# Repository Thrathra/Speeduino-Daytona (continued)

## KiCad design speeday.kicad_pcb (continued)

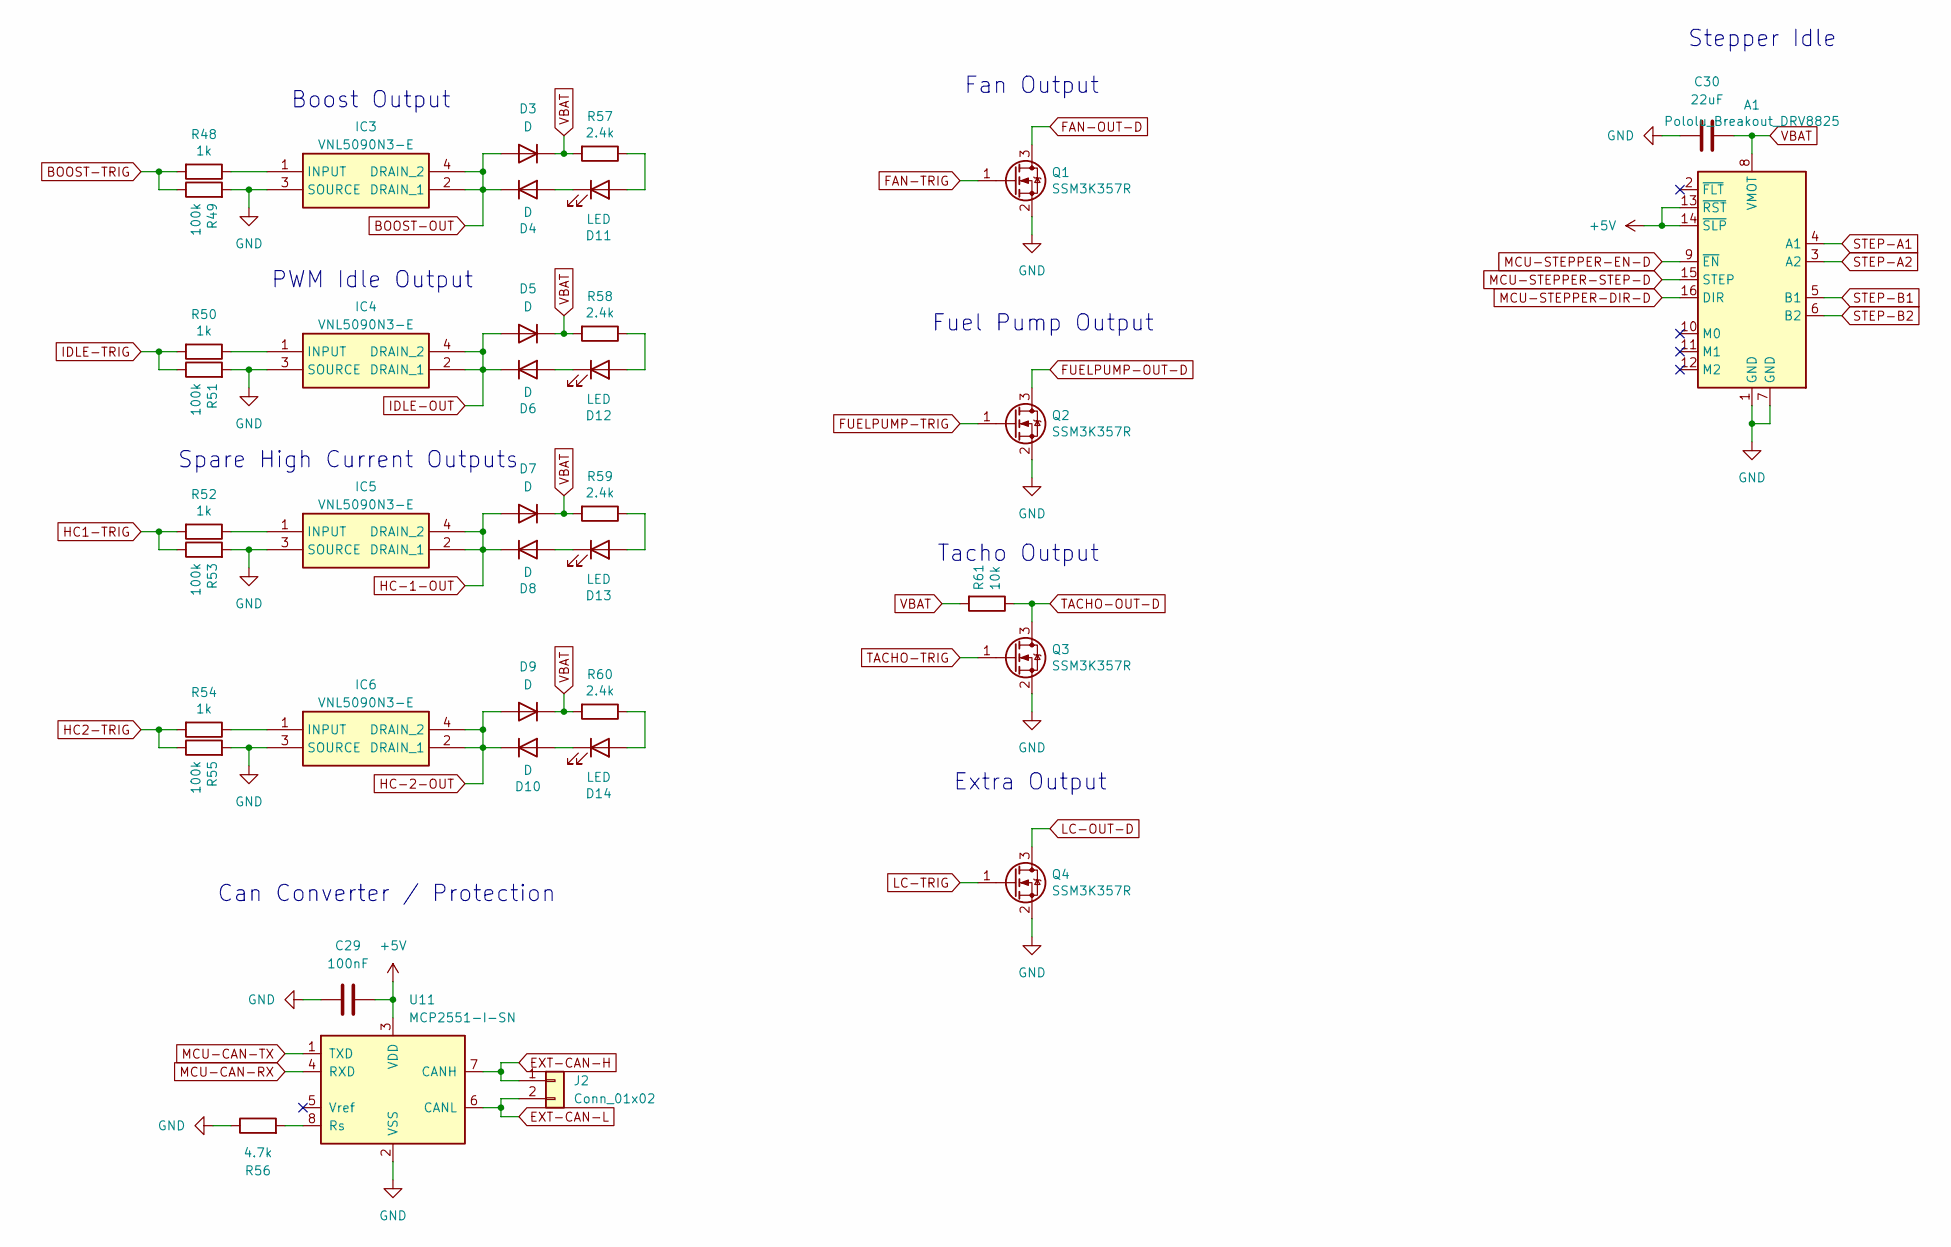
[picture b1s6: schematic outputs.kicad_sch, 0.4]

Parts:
A1: Pololu_Breakout_DRV8825; Pololu_Breakout-16_15.2x20.3mm
C29: 100nF; C_0805_2012Metric
C30: 22uF; C_0805_2012Metric
D3, D5, D7, D9: D; D_SOD-323
D4, D6, D8, D10: D; D_SOD-323; Manufacturer_Part_Number 1N4448WX-TP; Digikey Part Number 1N4448WXTPMSCT-ND
D11, D12, D13, D14: LED; LED_0805_2012Metric; Manufacturer_Part_Number LH R974-LP-1; Digikey Part Number 475-1415-1-ND
IC3, IC4, IC5, IC6: VNL5090N3-E; SOT230P700X180-4N; Manufacturer_Part_Number VNL5090N3-E
J2: Conn_01x02; PinHeader_1x02_P2.54mm_Vertical
Q1, Q2, Q3, Q4: SSM3K357R; SOT-23; Manufacturer_Part_Number SSM3K357R; Digikey Part Number SSM3K357RLFCT-ND
R48, R50, R52, R54: 1k; R_0805_2012Metric; Manufacturer_Part_Number RC0805FR-071KL; Digikey Part Number 311-1.00KCRCT-ND
R49, R51, R53, R55: 100k; R_0805_2012Metric; Manufacturer_Part_Number RC0805FR-07100KL; Digikey Part Number 311-100KCRCT-ND
R56: 4.7k; R_0805_2012Metric
R57, R58, R59, R60: 2.4k; R_0805_2012Metric; Manufacturer_Part_Number RC0805FR-072K4L; Digikey Part Number 311-2.40KCRCT-ND
R61: 10k; R_0805_2012Metric; Manufacturer_Part_Number RC0805JR-0710KL; Digikey Part Number 311-10KARCT-ND
U11: MCP2551-I-SN; SOIC-8_3.9x4.9mm_P1.27mm

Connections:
+5V: A1.13 (~RST), A1.14 (~SLP), C29.2, U11.3 (VDD); also elsewhere on the board
BOOST-OUT: D3.2 (A), D4.1 (K), IC3.2 (DRAIN_1), IC3.4 (DRAIN_2); also elsewhere on the board
BOOST-TRIG: R48.2, R49.1; also elsewhere on the board
EXT-CAN-H: J2.1, U11.7 (CANH)
EXT-CAN-L: J2.2, U11.6 (CANL)
FAN-OUT-D: Q1.3 (D); also elsewhere on the board
FAN-TRIG: Q1.1 (G); also elsewhere on the board
FUELPUMP-OUT-D: Q2.3 (D); also elsewhere on the board
FUELPUMP-TRIG: Q2.1 (G); also elsewhere on the board
GND: A1.1 (GND), A1.7 (GND), C29.1, C30.1, IC3.3 (SOURCE), IC4.3 (SOURCE), IC5.3 (SOURCE), IC6.3 (SOURCE), Q1.2 (S), Q2.2 (S), Q3.2 (S), Q4.2 (S), R49.2, R51.2, R53.2, R55.2, R56.1, U11.2 (VSS); also elsewhere on the board
HC1-TRIG: R52.2, R53.1; also elsewhere on the board
HC2-TRIG: R54.2, R55.1; also elsewhere on the board
HC-1-OUT: D7.2 (A), D8.1 (K), IC5.2 (DRAIN_1), IC5.4 (DRAIN_2); also elsewhere on the board
HC-2-OUT: D9.2 (A), D10.1 (K), IC6.2 (DRAIN_1), IC6.4 (DRAIN_2); also elsewhere on the board
IDLE-OUT: D5.2 (A), D6.1 (K), IC4.2 (DRAIN_1), IC4.4 (DRAIN_2); also elsewhere on the board
IDLE-TRIG: R50.2, R51.1; also elsewhere on the board
LC-OUT-D: Q4.3 (D); also elsewhere on the board
LC-TRIG: Q4.1 (G); also elsewhere on the board
MCU-CAN-RX: U11.4 (RXD); also elsewhere on the board
MCU-CAN-TX: U11.1 (TXD); also elsewhere on the board
MCU-STEPPER-DIR-D: A1.16 (DIR); also elsewhere on the board
MCU-STEPPER-EN-D: A1.9 (~EN); also elsewhere on the board
MCU-STEPPER-STEP-D: A1.15 (STEP); also elsewhere on the board
unnamed: D10.2 (A), D14.1 (K)
unnamed: D11.2 (A), R57.1
unnamed: D4.2 (A), D11.1 (K)
unnamed: D12.2 (A), R58.1
unnamed: D6.2 (A), D12.1 (K)
unnamed: D13.2 (A), R59.1
unnamed: D8.2 (A), D13.1 (K)
unnamed: D14.2 (A), R60.1
unnamed: IC3.1 (INPUT), R48.1
unnamed: IC4.1 (INPUT), R50.1
unnamed: IC5.1 (INPUT), R52.1
unnamed: IC6.1 (INPUT), R54.1
unnamed: R56.2, U11.8 (Rs)
STEP-A1: A1.4 (A1); also elsewhere on the board
STEP-A2: A1.3 (A2); also elsewhere on the board
STEP-B1: A1.5 (B1); also elsewhere on the board
STEP-B2: A1.6 (B2); also elsewhere on the board
TACHO-OUT-D: Q3.3 (D), R61.1; also elsewhere on the board
TACHO-TRIG: Q3.1 (G); also elsewhere on the board
VBAT: A1.8 (VMOT), C30.2, D3.1 (K), D5.1 (K), D7.1 (K), D9.1 (K), R57.2, R58.2, R59.2, R60.2, R61.2; also elsewhere on the board

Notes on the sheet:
Stepper Idle
Extra Output
PWM Idle Output
Spare High Current Outputs
Fan Output
Fuel Pump Output
Boost Output
Tacho Output
Can Converter / Protection

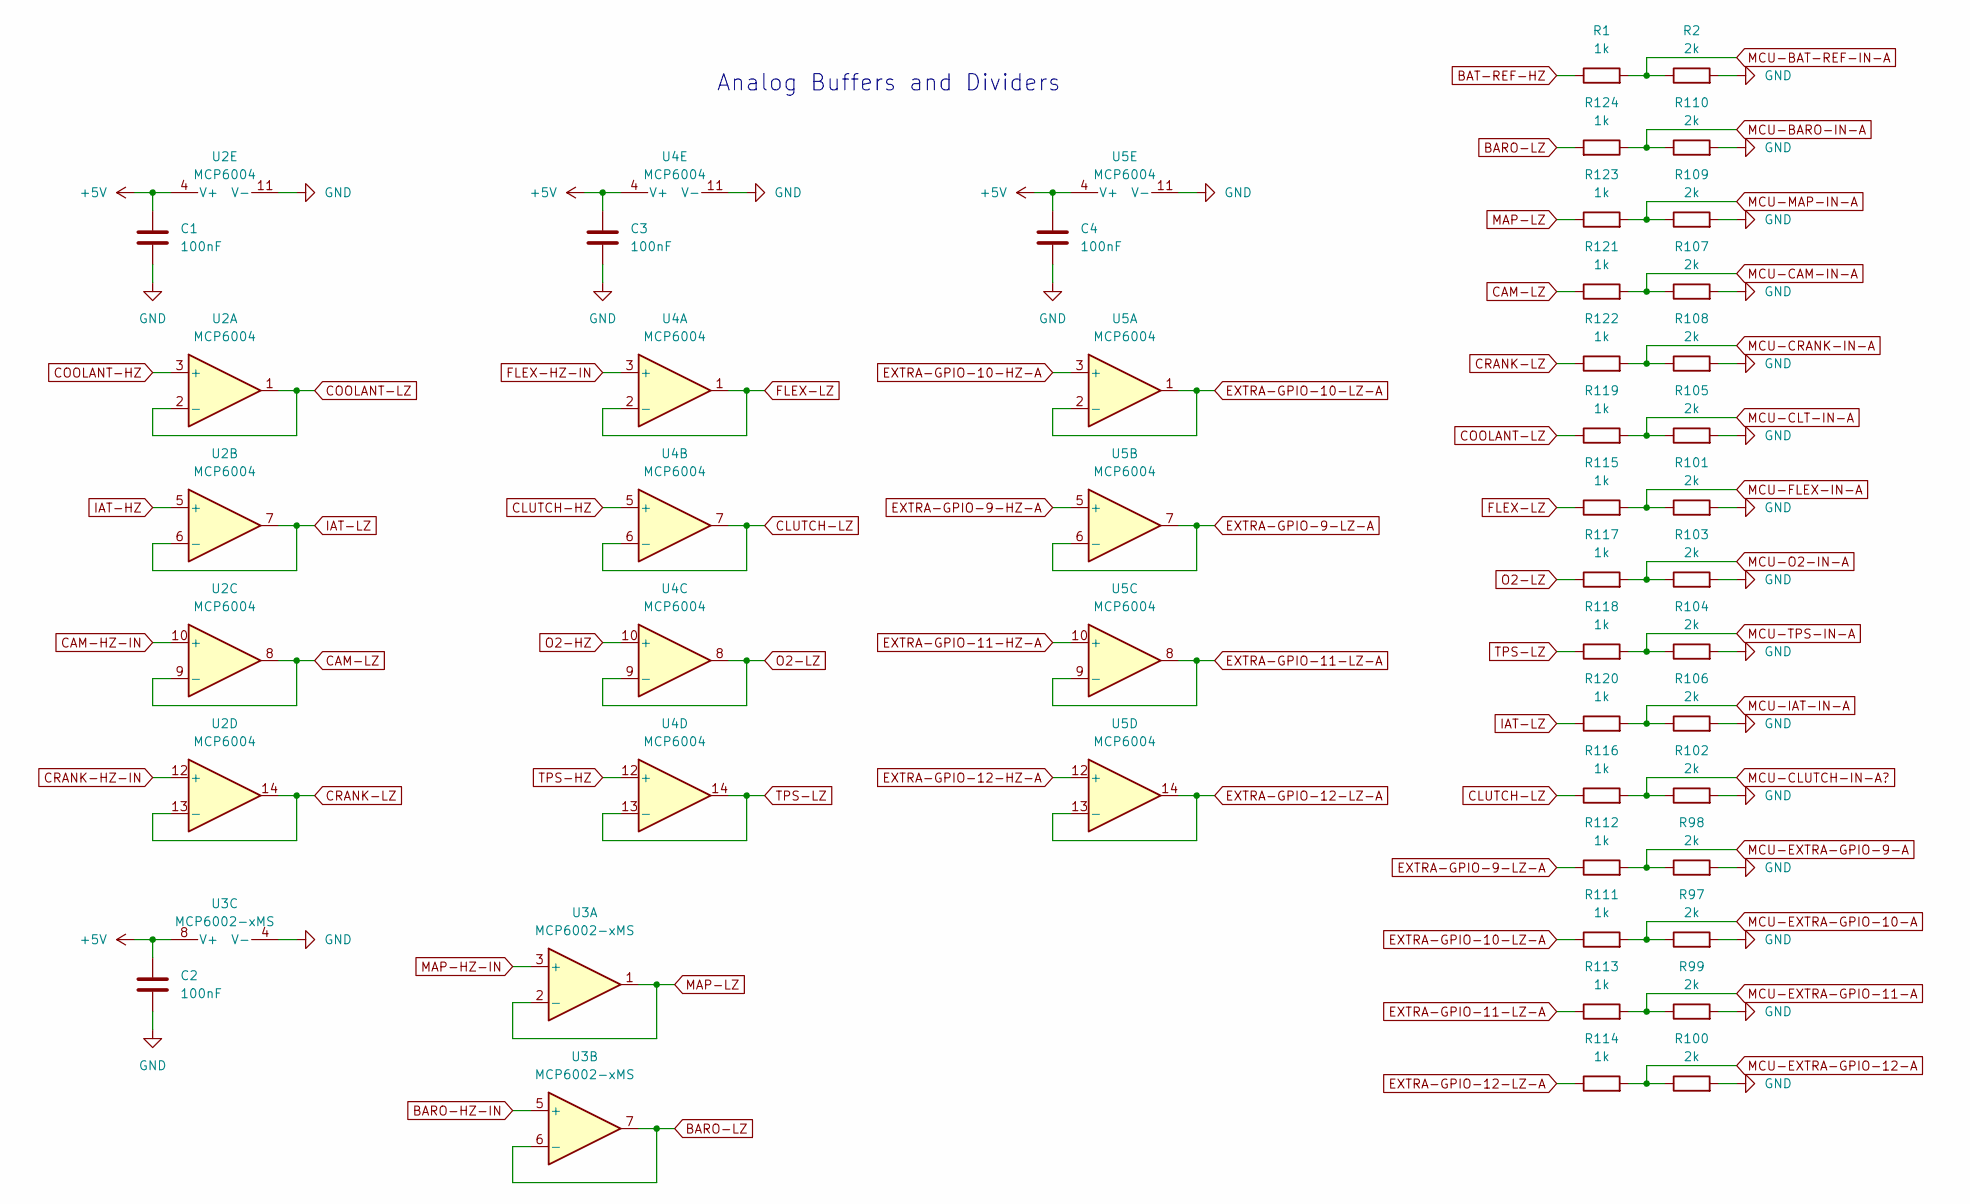
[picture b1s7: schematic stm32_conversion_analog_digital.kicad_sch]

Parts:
C1, C2, C3, C4: 100nF; C_0805_2012Metric
R1, R111, R112, R113, R114, R115, R116, R117, R118, R119, R120, R121, R122, R123, R124: 1k; R_0805_2012Metric
R2, R97, R98, R99, R100, R101, R102, R103, R104, R105, R106, R107, R108, R109, R110: 2k; R_0805_2012Metric
U2, U4, U5: MCP6004; TSSOP-14_4.4x5mm_P0.65mm
U3: MCP6002-xMS; TSSOP-8_4.4x3mm_P0.65mm

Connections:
+5V: C1.1, C2.1, C3.1, C4.1, U2.4 (V+), U3.8 (V+), U4.4 (V+), U5.4 (V+); also elsewhere on the board
BARO-HZ-IN: U3.5 (+); also elsewhere on the board
BARO-LZ: R124.2, U3.6 (-), U3.7
BAT-REF-HZ: R1.1; also elsewhere on the board
CAM-HZ-IN: U2.10 (+); also elsewhere on the board
CAM-LZ: R121.1, U2.8, U2.9 (-)
CLUTCH-HZ: U4.5 (+); also elsewhere on the board
CLUTCH-LZ: R116.1, U4.6 (-), U4.7
COOLANT-HZ: U2.3 (+); also elsewhere on the board
COOLANT-LZ: R119.1, U2.1, U2.2 (-)
CRANK-HZ-IN: U2.12 (+); also elsewhere on the board
CRANK-LZ: R122.1, U2.13 (-), U2.14
EXTRA-GPIO-9-HZ-A: U5.5 (+); also elsewhere on the board
EXTRA-GPIO-9-LZ-A: R112.1, U5.6 (-), U5.7
EXTRA-GPIO-10-HZ-A: U5.3 (+); also elsewhere on the board
EXTRA-GPIO-10-LZ-A: R111.1, U5.1, U5.2 (-)
EXTRA-GPIO-11-HZ-A: U5.10 (+); also elsewhere on the board
EXTRA-GPIO-11-LZ-A: R113.1, U5.8, U5.9 (-)
EXTRA-GPIO-12-HZ-A: U5.12 (+); also elsewhere on the board
EXTRA-GPIO-12-LZ-A: R114.1, U5.13 (-), U5.14
FLEX-HZ-IN: U4.3 (+); also elsewhere on the board
FLEX-LZ: R115.1, U4.1, U4.2 (-)
GND: C1.2, C2.2, C3.2, C4.2, R2.2, R97.2, R98.2, R99.2, R100.2, R101.2, R102.2, R103.2, R104.2, R105.2, R106.2, R107.2, R108.2, R109.2, R110.2, U2.11 (V-), U3.4 (V-), U4.11 (V-), U5.11 (V-); also elsewhere on the board
IAT-HZ: U2.5 (+); also elsewhere on the board
IAT-LZ: R120.1, U2.6 (-), U2.7
MAP-HZ-IN: U3.3 (+); also elsewhere on the board
MAP-LZ: R123.1, U3.1, U3.2 (-)
MCU-BARO-IN-A: R110.1, R124.1; also elsewhere on the board
MCU-BAT-REF-IN-A: R1.2, R2.1; also elsewhere on the board
MCU-CAM-IN-A: R107.1, R121.2; also elsewhere on the board
MCU-CLT-IN-A: R105.1, R119.2; also elsewhere on the board
MCU-CLUTCH-IN-A?: R102.1, R116.2; also elsewhere on the board
MCU-CRANK-IN-A: R108.1, R122.2; also elsewhere on the board
MCU-EXTRA-GPIO-9-A: R98.1, R112.2; also elsewhere on the board
MCU-EXTRA-GPIO-10-A: R97.1, R111.2; also elsewhere on the board
MCU-EXTRA-GPIO-11-A: R99.1, R113.2; also elsewhere on the board
MCU-EXTRA-GPIO-12-A: R100.1, R114.2; also elsewhere on the board
MCU-FLEX-IN-A: R101.1, R115.2; also elsewhere on the board
MCU-IAT-IN-A: R106.1, R120.2; also elsewhere on the board
MCU-MAP-IN-A: R109.1, R123.2; also elsewhere on the board
MCU-O2-IN-A: R103.1, R117.2; also elsewhere on the board
MCU-TPS-IN-A: R104.1, R118.2; also elsewhere on the board
O2-HZ: U4.10 (+); also elsewhere on the board
O2-LZ: R117.1, U4.8, U4.9 (-)
TPS-HZ: U4.12 (+); also elsewhere on the board
TPS-LZ: R118.1, U4.13 (-), U4.14

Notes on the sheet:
Analog Buffers and Dividers

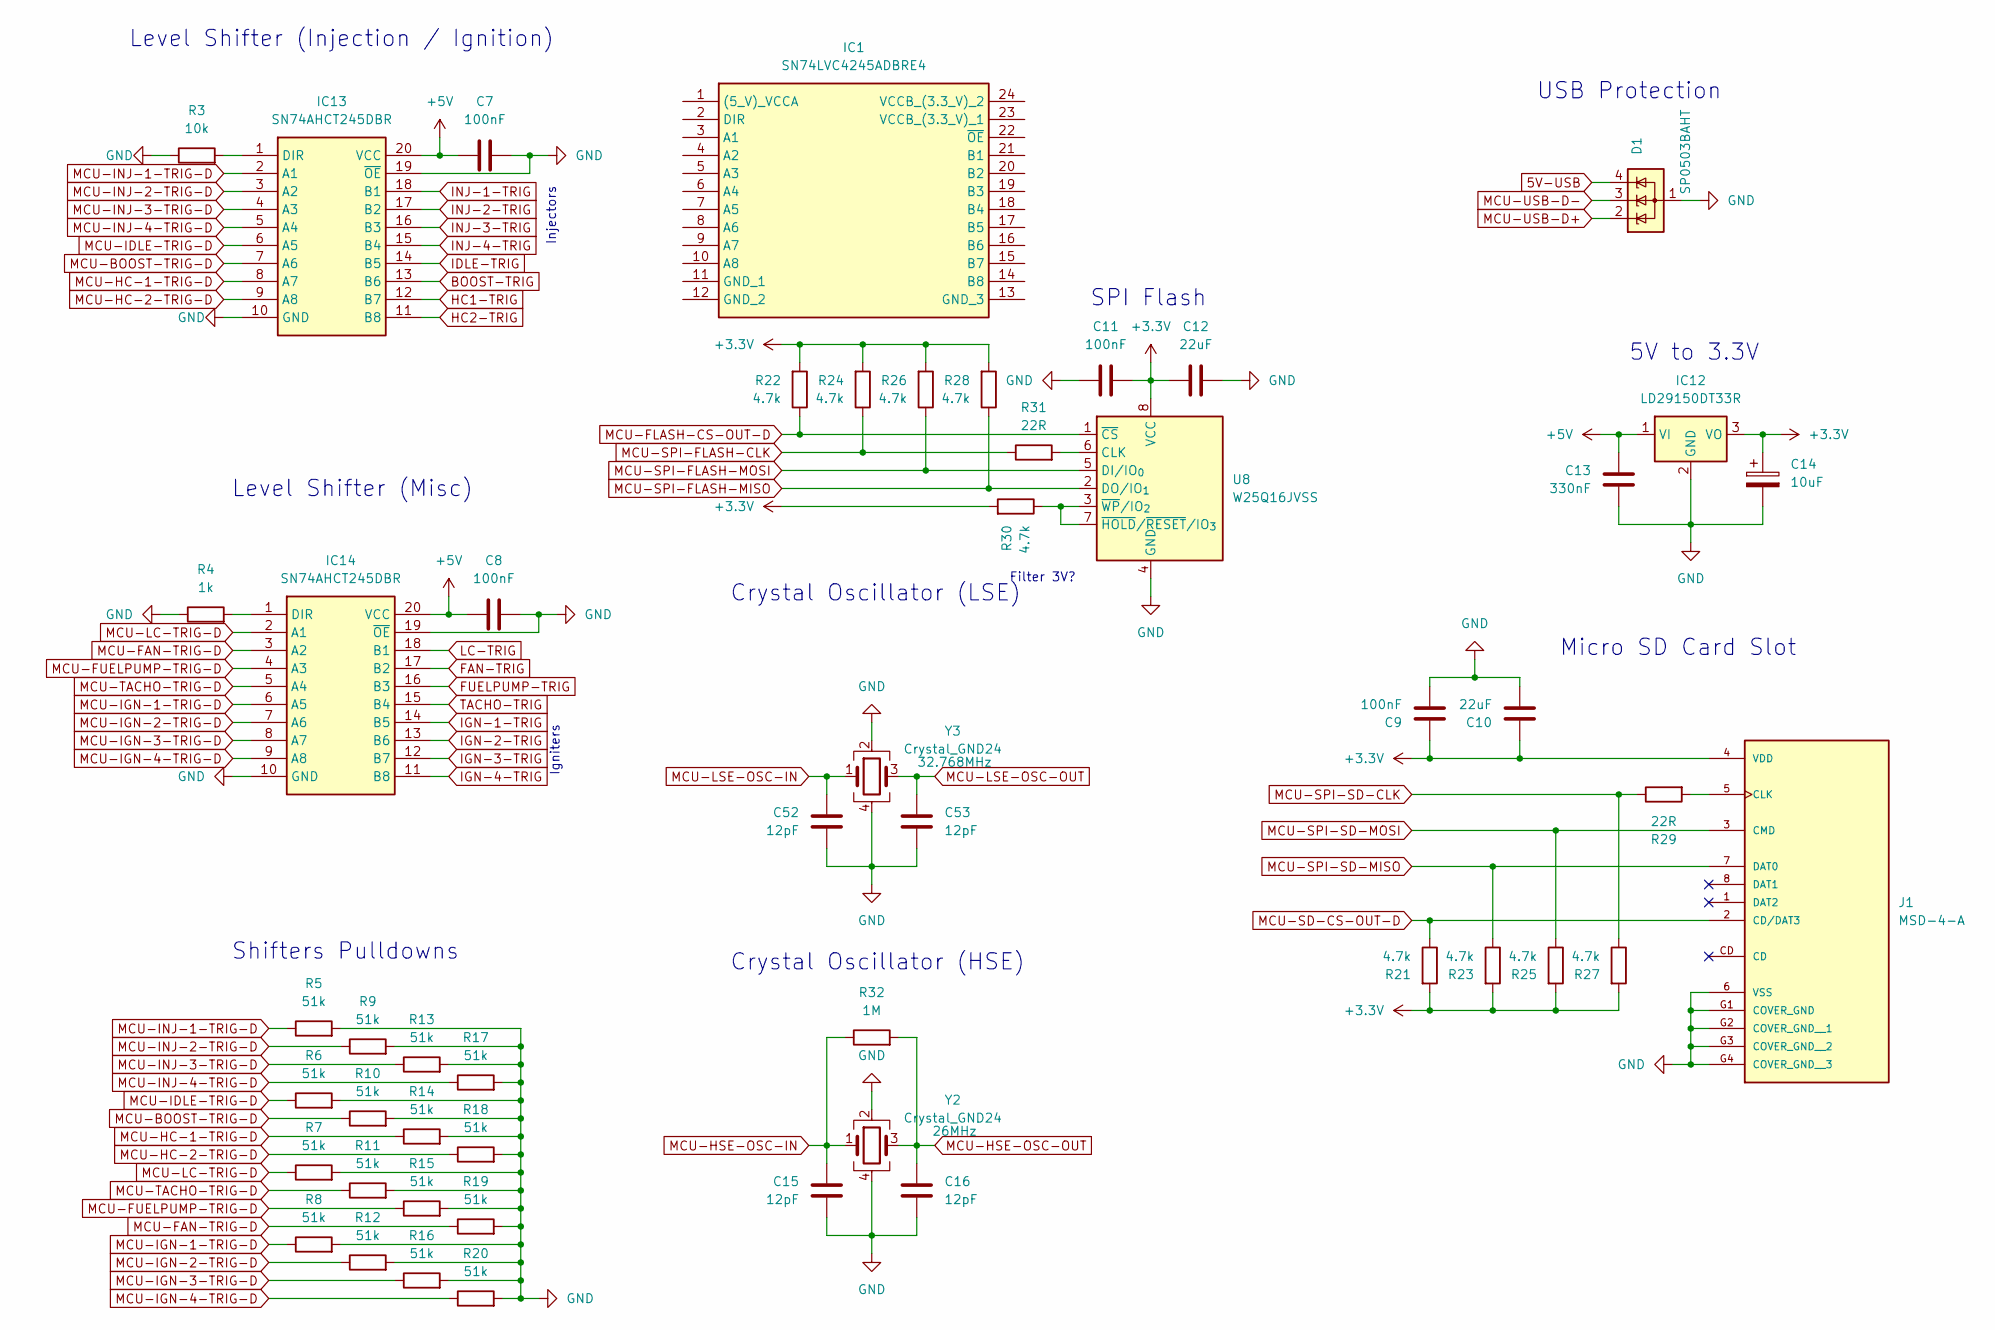
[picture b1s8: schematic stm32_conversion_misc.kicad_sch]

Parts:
C7, C8, C9, C11: 100nF; C_0805_2012Metric
C10, C12: 22uF; C_0805_2012Metric
C13: 330nF; C_0805_2012Metric
C14: 10uF; CP_EIA-3528-12_Kemet-T
C15, C16, C52, C53: 12pF; C_0805_2012Metric
D1: SP0503BAHT; SOT-143
IC1: SN74LVC4245ADBRE4; SOP65P780X200-24N; Manufacturer_Part_Number SN74LVC4245ADBRE4; Mouser Part Number 595-SN74LVC4245ADBRE
IC12: LD29150DT33R; TO-252-2; Manufacturer_Part_Number LD29150DT33R; Mouser Part Number 511-LD29150DT33R
IC13, IC14: SN74AHCT245DBR; SOP65P780X200-20N; Manufacturer_Part_Number SN74AHCT245DBR; Mouser Part Number 595-SN74AHCT245DBR
J1: MSD-4-A; CUI_MSD-4-A; PARTREV 1.0
R3: 10k; R_0805_2012Metric
R4: 1k; R_0805_2012Metric
R5, R6, R7, R8, R9, R10, R11, R12, R13, R14, R15, R16, R17, R18, R19, R20: 51k; R_0805_2012Metric
R21, R22, R23, R24, R25, R26, R27, R28, R30: 4.7k; R_0805_2012Metric
R29, R31: 22R; R_0805_2012Metric
R32: 1M; R_0805_2012Metric
U8: W25Q16JVSS; SOIC-8_5.3x5.3mm_P1.27mm
Y2, Y3: Crystal_GND24; Crystal_SMD_2016-4Pin_2.0x1.6mm

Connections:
5V-USB: D1.4 (K); also elsewhere on the board
+3.3V: C9.2, C10.2, C11.2, C12.1, C14.1, IC12.3 (VO), J1.4 (VDD), R21.2, R22.2, R23.2, R24.2, R25.2, R26.2, R27.2, R28.2, R30.2, U8.8 (VCC); also elsewhere on the board
+5V: C7.1, C8.1, C13.1, IC12.1 (VI), IC13.20 (VCC), IC14.20 (VCC); also elsewhere on the board
BOOST-TRIG: IC13.13 (B6); also elsewhere on the board
FAN-TRIG: IC14.17 (B2); also elsewhere on the board
FUELPUMP-TRIG: IC14.16 (B3); also elsewhere on the board
GND: C7.2, C8.2, C9.1, C10.1, C11.1, C12.2, C13.2, C14.2, C15.2, C16.2, C52.2, C53.2, D1.1 (A), IC12.2 (GND), IC13.10 (GND), IC13.19 (~OE), IC14.10 (GND), IC14.19 (~OE), J1.6 (VSS), J1.G1 (COVER_GND), J1.G2 (COVER_GND__1), J1.G3 (COVER_GND__2), J1.G4 (COVER_GND__3), R3.1, R4.1, R5.2, R6.2, R7.2, R8.2, R9.2, R10.2, R11.2, R12.2, R13.2, R14.2, R15.2, R16.2, R17.2, R18.2, R19.2, R20.2, U8.4 (GND), Y2.2, Y2.4, Y3.2, Y3.4; also elsewhere on the board
HC1-TRIG: IC13.12 (B7); also elsewhere on the board
HC2-TRIG: IC13.11 (B8); also elsewhere on the board
IDLE-TRIG: IC13.14 (B5); also elsewhere on the board
IGN-1-TRIG: IC14.14 (B5); also elsewhere on the board
IGN-2-TRIG: IC14.13 (B6); also elsewhere on the board
IGN-3-TRIG: IC14.12 (B7); also elsewhere on the board
IGN-4-TRIG: IC14.11 (B8); also elsewhere on the board
INJ-1-TRIG: IC13.18 (B1); also elsewhere on the board
INJ-2-TRIG: IC13.17 (B2); also elsewhere on the board
INJ-3-TRIG: IC13.16 (B3); also elsewhere on the board
INJ-4-TRIG: IC13.15 (B4); also elsewhere on the board
LC-TRIG: IC14.18 (B1); also elsewhere on the board
MCU-BOOST-TRIG-D: IC13.7 (A6), R10.1; also elsewhere on the board
MCU-FAN-TRIG-D: IC14.3 (A2), R19.1; also elsewhere on the board
MCU-FLASH-CS-OUT-D: R22.1, U8.1 (~CS); also elsewhere on the board
MCU-FUELPUMP-TRIG-D: IC14.4 (A3), R15.1; also elsewhere on the board
MCU-HC-1-TRIG-D: IC13.8 (A7), R14.1; also elsewhere on the board
MCU-HC-2-TRIG-D: IC13.9 (A8), R18.1; also elsewhere on the board
MCU-HSE-OSC-IN: C15.1, R32.1, Y2.1; also elsewhere on the board
MCU-HSE-OSC-OUT: C16.1, R32.2, Y2.3; also elsewhere on the board
MCU-IDLE-TRIG-D: IC13.6 (A5), R6.1; also elsewhere on the board
MCU-IGN-1-TRIG-D: IC14.6 (A5), R8.1; also elsewhere on the board
MCU-IGN-2-TRIG-D: IC14.7 (A6), R12.1; also elsewhere on the board
MCU-IGN-3-TRIG-D: IC14.8 (A7), R16.1; also elsewhere on the board
MCU-IGN-4-TRIG-D: IC14.9 (A8), R20.1; also elsewhere on the board
MCU-INJ-1-TRIG-D: IC13.2 (A1), R5.1; also elsewhere on the board
MCU-INJ-2-TRIG-D: IC13.3 (A2), R9.1; also elsewhere on the board
MCU-INJ-3-TRIG-D: IC13.4 (A3), R13.1; also elsewhere on the board
MCU-INJ-4-TRIG-D: IC13.5 (A4), R17.1; also elsewhere on the board
MCU-LC-TRIG-D: IC14.2 (A1), R7.1; also elsewhere on the board
MCU-LSE-OSC-IN: C52.1, Y3.1; also elsewhere on the board
MCU-LSE-OSC-OUT: C53.1, Y3.3; also elsewhere on the board
MCU-SD-CS-OUT-D: J1.2 (CD/DAT3), R21.1; also elsewhere on the board
MCU-SPI-FLASH-CLK: R24.1, R31.1; also elsewhere on the board
MCU-SPI-FLASH-MISO: R28.1, U8.2 (DO/IO_{1}); also elsewhere on the board
MCU-SPI-FLASH-MOSI: R26.1, U8.5 (DI/IO_{0}); also elsewhere on the board
MCU-SPI-SD-CLK: R27.1, R29.1; also elsewhere on the board
MCU-SPI-SD-MISO: J1.7 (DAT0), R23.1; also elsewhere on the board
MCU-SPI-SD-MOSI: J1.3 (CMD), R25.1; also elsewhere on the board
MCU-TACHO-TRIG-D: IC14.5 (A4), R11.1; also elsewhere on the board
MCU-USB-D+: D1.2 (K); also elsewhere on the board
MCU-USB-D-: D1.3 (K); also elsewhere on the board
unnamed: IC13.1 (DIR), R3.2
unnamed: IC14.1 (DIR), R4.2
unnamed: J1.5 (CLK), R29.2
unnamed: R31.2, U8.6 (CLK)
unnamed: R30.1, U8.3 (~WP/IO_{2}), U8.7 (~HOLD/~RESET/IO_{3})
TACHO-TRIG: IC14.15 (B4); also elsewhere on the board

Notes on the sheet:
5V to 3.3V
Filter 3V?
USB Protection
Shifters Pulldowns
Injectors
Crystal Oscillator (HSE)
Level Shifter (Injection / Ignition)
SPI Flash
Level Shifter (Misc)
Igniters
Crystal Oscillator (LSE)
Micro SD Card Slot

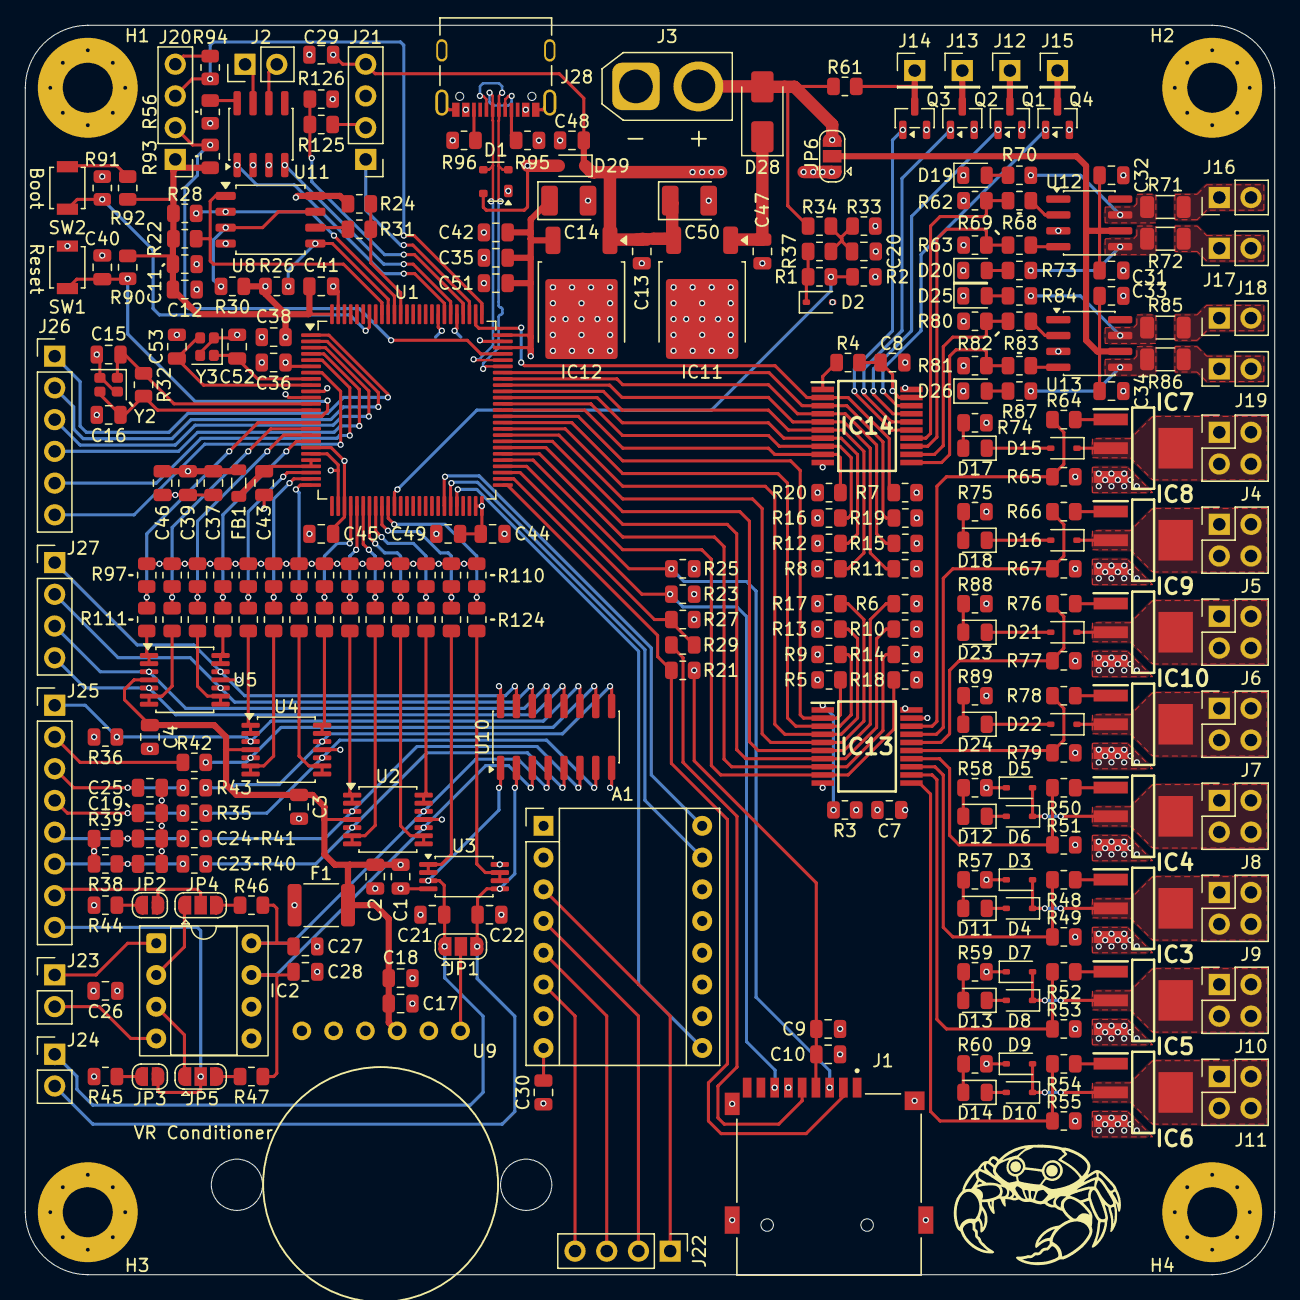
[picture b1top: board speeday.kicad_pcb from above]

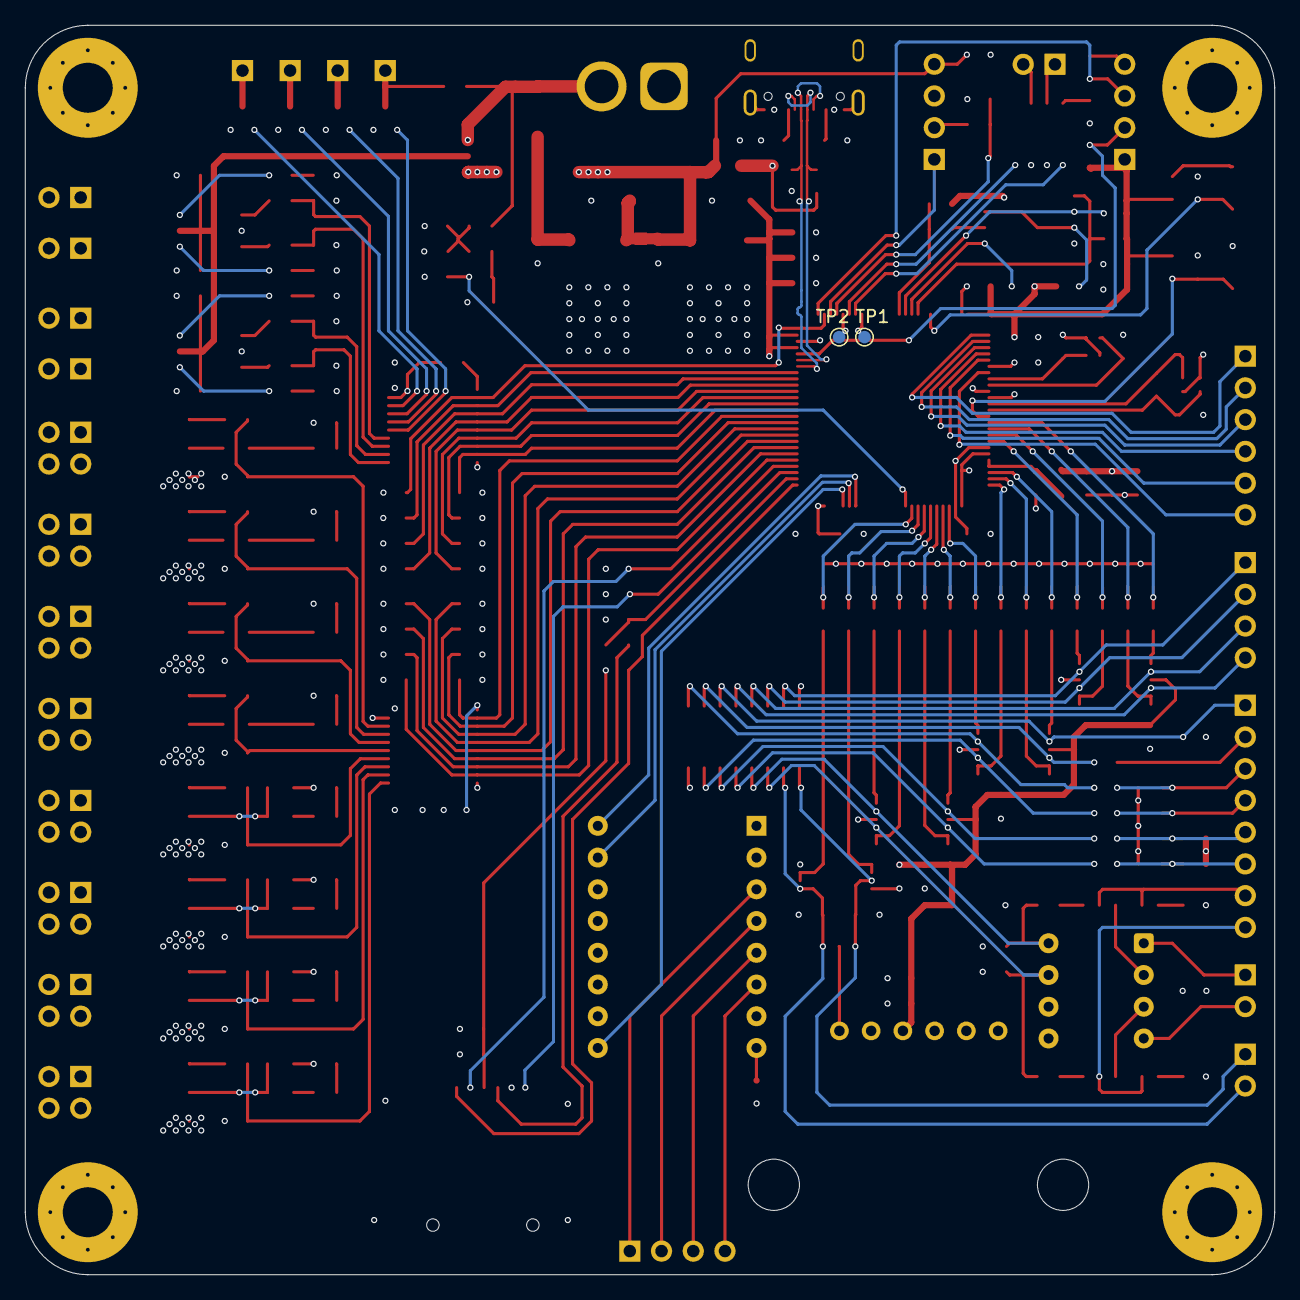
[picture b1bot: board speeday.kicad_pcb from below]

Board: 4 copper layers, 100.0 x 100.0 mm, 281 parts (2 on the bottom side), 204 nets.

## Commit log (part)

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2025-04-03 Populate Board
2025-04-18 Add additional IOs
2025-05-19 Pre MCU switch
2025-05-28 Fix MCU decoupling capacitors
2025-05-31 Update from Speeduino Discord suggestions (thanks to Detonator)
2025-06-30 Fully connect all components
2025-11-04 Fix power traces width and add logo
2025-11-09 Updated reference layout
2026-06-29 Change power layout, add low frequency crystal
